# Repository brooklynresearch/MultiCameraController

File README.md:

MultiCameraController
======================

Board designs for controlling 12 DSLR cameras

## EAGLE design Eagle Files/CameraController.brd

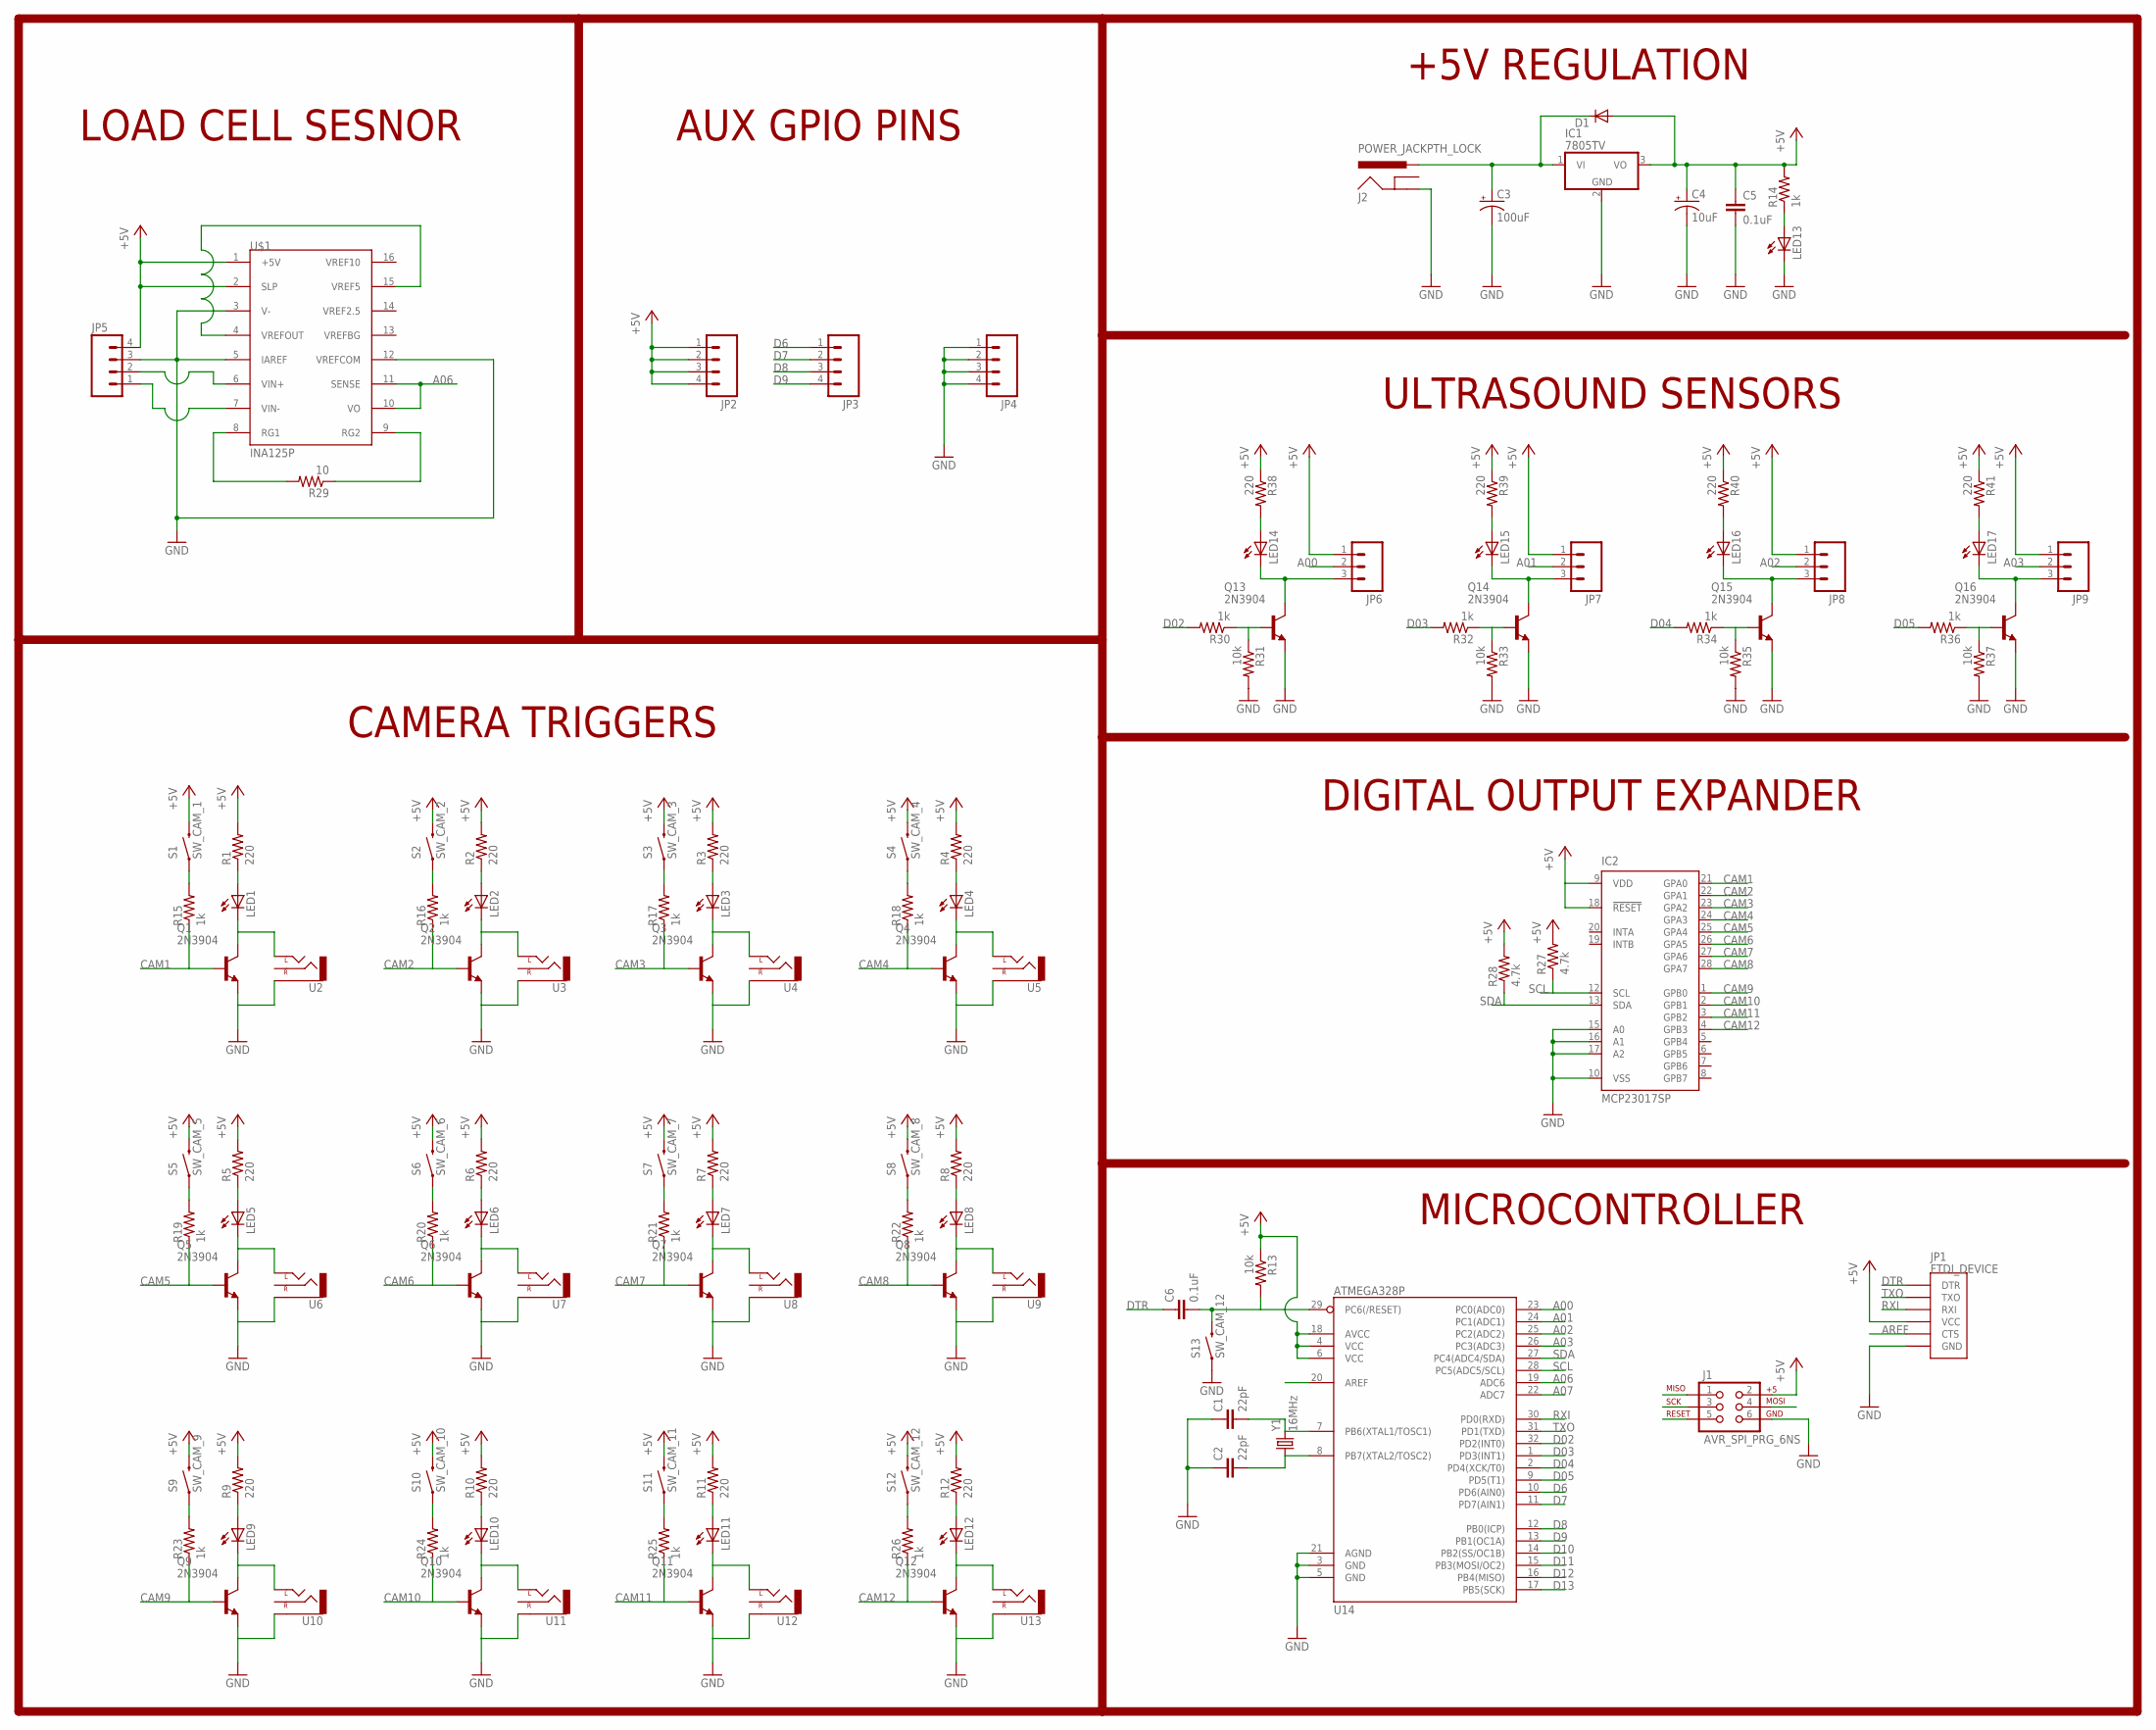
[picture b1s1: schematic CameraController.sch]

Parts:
C1, C2: 22pF; CAP-PTH-SMALL2
C3: 100uF; E2,5-7
C4: 10uF; E2,5-5
C5, C6: 0.1uF; C025-025X050
D1: DIODEPTH; DIODE-1N4001
IC1: 7805TV; TO220V
IC2: MCP23017SP; DIL28-3
J1: AVR_SPI_PRG_6NS; 2X3-NS
J2: POWER_JACKPTH_LOCK; POWER_JACK_PTH_LOCK
JP1: FTDI_DEVICE; FTDI_DEVICE_SIDE
JP2, JP3, JP4: M04PTH; 1X04
JP5: M04LONGPADS; 1X04_LONGPADS
JP6, JP7, JP8, JP9: M03LONGPADS; 1X03_LONGPADS
LED1, LED2, LED3, LED4, LED5, LED6, LED7, LED8, LED9, LED10, LED11, LED12, LED13, LED14, LED15, LED16, LED17: LED5MM
Q1, Q2, Q3, Q4, Q5, Q6, Q7, Q8, Q9, Q10, Q11, Q12, Q13, Q14, Q15, Q16: 2N3904; TO92
R1, R2, R3, R4, R5, R6, R7, R8, R9, R10, R11, R12, R38, R39, R40, R41: 220; 0207/10
R13, R31, R33, R35, R37: 10k; 0207/10
R14, R15, R16, R17, R18, R19, R20, R21, R22, R23, R24, R25, R26, R30, R32, R34, R36: 1k; 0207/10
R27, R28: 4.7k; 0207/10
R29: 10; 0207/10
S1: SW_CAM_1; TACTILE-PTH
S2: SW_CAM_2; TACTILE-PTH
S3: SW_CAM_3; TACTILE-PTH
S4: SW_CAM_4; TACTILE-PTH
S5: SW_CAM_5; TACTILE-PTH
S6: SW_CAM_6; TACTILE-PTH
S7: SW_CAM_7; TACTILE-PTH
S8: SW_CAM_8; TACTILE-PTH
S9: SW_CAM_9; TACTILE-PTH
S10: SW_CAM_10; TACTILE-PTH
S11: SW_CAM_11; TACTILE-PTH
S12, S13: SW_CAM_12; TACTILE-PTH
U2, U3, U4, U5, U6, U7, U8, U9, U10, U11, U12, U13: AUDIO-JACKSPECIAL_POGO_PINS; STEREOJACK2.5MM_SPECIA_POGOPINS
U14: ATMEGA328P; TQFP32-08
U$1: INA125P; 16-DIP
Y1: 16MHz; HC49US

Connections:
+5V: C4.+, C5.1, D1.A, IC1.3 (VO), IC2.9 (VDD), IC2.18 (!RESET), J1.2, JP1.P$4 (VCC), JP2.1, JP2.2, JP2.3, JP2.4, JP5.4, JP6.1, JP7.1, JP8.1, JP9.1, R1.2, R2.2, R3.2, R4.2, R5.2, R6.2, R7.2, R8.2, R9.2, R10.2, R11.2, R12.2, R13.1, R14.2, R27.2, R28.2, R38.1, R39.1, R40.1, R41.1, S1.3 (2), S2.3 (2), S3.3 (2), S4.3 (2), S5.3 (2), S6.3 (2), S7.3 (2), S8.3 (2), S9.3 (2), S10.3 (2), S11.3 (2), S12.3 (2), U14.4 (VCC), U14.6 (VCC), U14.18 (AVCC), U$1.1 (+5V), U$1.2 (SLP)
A00: JP6.2, U14.23 (PC0(ADC0))
A01: JP7.2, U14.24 (PC1(ADC1))
A02: JP8.2, U14.25 (PC2(ADC2))
A03: JP9.2, U14.26 (PC3(ADC3))
A06: U14.19 (ADC6), U$1.10 (VO), U$1.11 (SENSE)
A07: U14.22 (ADC7)
AREF: JP1.P$5 (CTS), U14.20 (AREF)
CAM1: IC2.21 (GPA0), Q1.2 (B), R15.1
CAM2: IC2.22 (GPA1), Q2.2 (B), R16.1
CAM3: IC2.23 (GPA2), Q3.2 (B), R17.1
CAM4: IC2.24 (GPA3), Q4.2 (B), R18.1
CAM5: IC2.25 (GPA4), Q5.2 (B), R19.1
CAM6: IC2.26 (GPA5), Q6.2 (B), R20.1
CAM7: IC2.27 (GPA6), Q7.2 (B), R21.1
CAM8: IC2.28 (GPA7), Q8.2 (B), R22.1
CAM9: IC2.1 (GPB0), Q9.2 (B), R23.1
CAM10: IC2.2 (GPB1), Q10.2 (B), R24.1
CAM11: IC2.3 (GPB2), Q11.2 (B), R25.1
CAM12: IC2.4 (GPB3), Q12.2 (B), R26.1
D02: R30.2, U14.32 (PD2(INT0))
D03: R32.2, U14.1 (PD3(INT1))
D04: R34.2, U14.2 (PD4(XCK/T0))
D05: R36.2, U14.9 (PD5(T1))
D6: JP3.1, U14.10 (PD6(AIN0))
D7: JP3.2, U14.11 (PD7(AIN1))
D8: JP3.3, U14.12 (PB0(ICP))
D9: JP3.4, U14.13 (PB1(OC1A))
D10: U14.14 (PB2(SS/OC1B))
D11: J1.4, U14.15 (PB3(MOSI/OC2))
D12: J1.1, U14.16 (PB4(MISO))
D13: J1.3, U14.17 (PB5(SCK))
DTR: C6.1, JP1.P$1 (DTR)
GND: C1.1, C2.1, C3.-, C4.-, C5.2, IC1.2 (GND), IC2.10 (VSS), IC2.15 (A0), IC2.16 (A1), IC2.17 (A2), J1.6, J2.GND, JP1.P$6 (GND), JP4.1, JP4.2, JP4.3, JP4.4, JP5.3, LED13.K (C), Q1.3 (E), Q2.3 (E), Q3.3 (E), Q4.3 (E), Q5.3 (E), Q6.3 (E), Q7.3 (E), Q8.3 (E), Q9.3 (E), Q10.3 (E), Q11.3 (E), Q12.3 (E), Q13.3 (E), Q14.3 (E), Q15.3 (E), Q16.3 (E), R31.2, R33.2, R35.2, R37.2, S13.1, U2.RING1 (SLEEVE), U3.RING1 (SLEEVE), U4.RING1 (SLEEVE), U5.RING1 (SLEEVE), U6.RING1 (SLEEVE), U7.RING1 (SLEEVE), U8.RING1 (SLEEVE), U9.RING1 (SLEEVE), U10.RING1 (SLEEVE), U11.RING1 (SLEEVE), U12.RING1 (SLEEVE), U13.RING1 (SLEEVE), U14.3 (GND), U14.5 (GND), U14.21 (AGND), U$1.3 (V-), U$1.5 (IAREF), U$1.12 (VREFCOM)
unnamed: LED1.K (C), Q1.1 (C), U2.SHIELD (LEFT)
unnamed: LED1.A, R1.1
unnamed: LED2.K (C), Q2.1 (C), U3.SHIELD (LEFT)
unnamed: LED2.A, R2.1
unnamed: LED3.K (C), Q3.1 (C), U4.SHIELD (LEFT)
unnamed: LED3.A, R3.1
unnamed: LED4.K (C), Q4.1 (C), U5.SHIELD (LEFT)
unnamed: LED4.A, R4.1
unnamed: LED5.K (C), Q5.1 (C), U6.SHIELD (LEFT)
unnamed: LED5.A, R5.1
unnamed: LED6.K (C), Q6.1 (C), U7.SHIELD (LEFT)
unnamed: LED6.A, R6.1
unnamed: LED7.K (C), Q7.1 (C), U8.SHIELD (LEFT)
unnamed: LED7.A, R7.1
unnamed: LED8.K (C), Q8.1 (C), U9.SHIELD (LEFT)
unnamed: LED8.A, R8.1
unnamed: LED9.K (C), Q9.1 (C), U10.SHIELD (LEFT)
unnamed: LED9.A, R9.1
unnamed: LED10.K (C), Q10.1 (C), U11.SHIELD (LEFT)
unnamed: LED10.A, R10.1
unnamed: LED11.K (C), Q11.1 (C), U12.SHIELD (LEFT)
unnamed: LED11.A, R11.1
unnamed: LED12.K (C), Q12.1 (C), U13.SHIELD (LEFT)
unnamed: LED12.A, R12.1
unnamed: Q13.2 (B), R30.1, R31.1
unnamed: C3.+, D1.C, IC1.1 (VI), J2.PWR
unnamed: Q14.2 (B), R32.1, R33.1
unnamed: JP6.3, LED14.K (C), Q13.1 (C)
unnamed: JP7.3, LED15.K (C), Q14.1 (C)
unnamed: C1.2, U14.7 (PB6(XTAL1/TOSC1)), Y1.2
unnamed: C2.2, U14.8 (PB7(XTAL2/TOSC2)), Y1.1
unnamed: LED13.A, R14.1
unnamed: JP5.2, U$1.6 (VIN+)
unnamed: R29.2, U$1.8 (RG1)
unnamed: R15.2, S1.1
unnamed: R16.2, S2.1
unnamed: R17.2, S3.1
unnamed: R18.2, S4.1
unnamed: R19.2, S5.1
unnamed: R20.2, S6.1
unnamed: R21.2, S7.1
unnamed: R22.2, S8.1
unnamed: R23.2, S9.1
unnamed: R24.2, S10.1
unnamed: R25.2, S11.1
unnamed: R26.2, S12.1
unnamed: U$1.4 (VREFOUT), U$1.15 (VREF5)
unnamed: JP5.1, U$1.7 (VIN-)
unnamed: R29.1, U$1.9 (RG2)
unnamed: Q15.2 (B), R34.1, R35.1
unnamed: JP8.3, LED16.K (C), Q15.1 (C)
unnamed: Q16.2 (B), R36.1, R37.1
unnamed: JP9.3, LED17.K (C), Q16.1 (C)
unnamed: LED14.A, R38.2
unnamed: LED15.A, R39.2
unnamed: LED16.A, R40.2
unnamed: LED17.A, R41.2
RST: C6.2, J1.5, R13.2, S13.3 (2), U14.29 (PC6(/RESET))
RXI: JP1.P$3 (RXI), U14.30 (PD0(RXD))
SCL: IC2.12 (SCL), R27.1, U14.28 (PC5(ADC5/SCL))
SDA: IC2.13 (SDA), R28.1, U14.27 (PC4(ADC4/SDA))
TXO: JP1.P$2 (TXO), U14.31 (PD1(TXD))

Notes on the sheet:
+5V REGULATION
MICROCONTROLLER
CAMERA TRIGGERS
DIGITAL OUTPUT EXPANDER
AUX GPIO PINS
ULTRASOUND SENSORS
LOAD CELL SESNOR

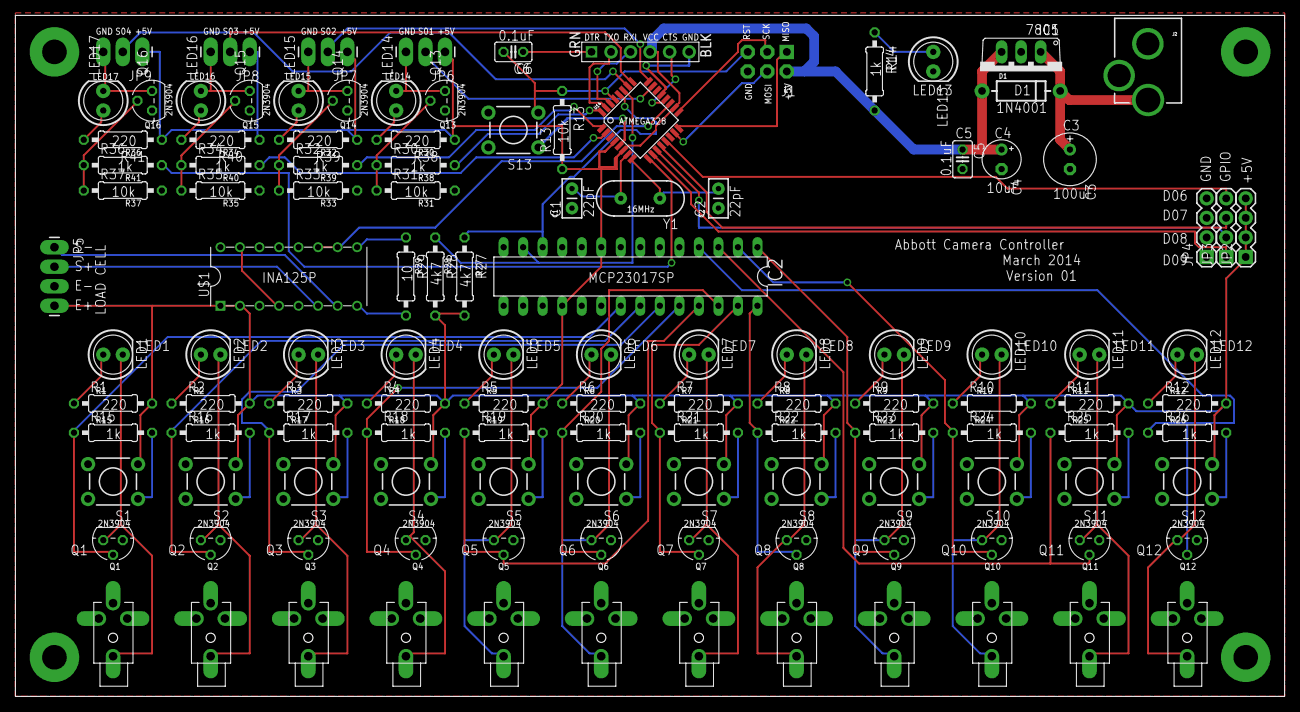
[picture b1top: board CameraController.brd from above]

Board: 2 copper layers, 165.1 x 88.6 mm, 122 parts (0 on the bottom side), 94 nets.

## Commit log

2014-02-21 Initial Schematic and Layout
    Initial Trigger Board and Layout. Still needs silkscreen, sensor
    inputs, and approvals.
2014-03-03 Eagle Files To Be Fabricated
    Added Ultrasound Breakout, Load Cell Breakout, Aux Breakout, Resistors
    to Switches. Changed Arduino Profile.
2014-03-10 Initial Arduino Code
    Uploaded some test code for Arduino. It
2014-03-12 Updates from initial setup
2014-03-12 Adding timing experiments and backwards traversal attempt
2014-03-13 New code for timing and outputs
2018-03-05 Making Things Publicable
    Removed "Abbott" from everything

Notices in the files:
parts and their libraries:
SparkFun-DigitalIC: Licensing: CC v3.0 Share-Alike You are welcome to use this library for commercial purposes.
